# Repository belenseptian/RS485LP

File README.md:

-----

# RS-485LP (Low Power RS485 Node)

**RS-485LP** is an open-source RS485 converter featuring a custom PCB and optimized PlatformIO firmware. It is designed to minimize power consumption for battery-operated sensors and remote monitoring systems.

🔗 **Official Project Website:** [https://belenseptian.github.io/RS485LP/](https://belenseptian.github.io/RS485LP/)

-----

### 📟 Board Design Preview
Below are the top and bottom views of the RS-485LP PCB.

| Top View (Components) | Bottom View (Traces) |
| :---: | :---: |
|  |  |

-----

## 🚀 Features

  * **Sleep & Shutdown Optimization:** Optimized for deep-sleep and hardware shutdown modes to achieve micro-amp current draw during periods of inactivity.
  * **RS485 Protocol:** Reliable differential signaling for long-range data transmission.
  * **PlatformIO Integrated:** Easy-to-compile and upload firmware using VS Code.
  * **Compact Form Factor:** Small PCB footprint suitable for tight enclosures.

-----

## 🛠 Hardware Fabrication

### 1\. Obtain KiCad Files

The PCB design is created using **KiCad**. You can find the project files in the `pcb/` directory.

1.  Clone this repository to get the full KiCad project.
2.  Open the project in KiCad to view the schematic or modify the layout.

### 2\. Ordering from PCBWay (or similar)

Most modern PCB manufacturers allow you to upload the KiCad file directly:

1.  **Option A (Direct):** Upload the `.kicad_pcb` file from the `pcb/` folder directly to [PCBWay's Instant Quote](https://www.pcbway.com/).
2.  **Option B (Manual Gerber Export):** - In KiCad, go to **File \> Fabrication Outputs \> Gerbers (.gbr)**.
      - Generate the drill files and zip all outputs together.
      - Upload the resulting `.zip` file to the manufacturer.

-----

## 💻 Software Setup

This project uses **PlatformIO** inside **Visual Studio Code**.

### Prerequisites

  * **VS Code:** [Download here](https://code.visualstudio.com/)
  * **PlatformIO IDE Extension:** Install this via the VS Code Extensions marketplace.

### Project Installation

1.  Clone the repository:
    ```bash
    git clone https://github.com/belenseptian/RS485LP.git
    ```
2.  Open VS Code and go to **PlatformIO Home** \> **Open Project**.
3.  Navigate to the `firmware/` folder and select it.

-----

## 📤 Uploading & Testing Sleep Mode

1.  **Connect Hardware:** Connect your board to your computer using a USB-to-Serial adapter.
2.  **Build & Upload:** Use the **Checkmark (✅)** to compile and the **Arrow (➡️)** to flash.
3.  **Verify Shutdown:**
      - Open the **Serial Monitor (🔌)** (Baud rate: `115200`).
      - The monitor should display "Entering Sleep Mode..." or "Shutting Down...".
      - Use a Multimeter or Power Profiler to measure the current draw; it should drop significantly as the MCU enters the deep sleep/shutdown state.
4.  **Wake-up Trigger:** Ensure you have configured the wake-up source (e.g., Timer or External Interrupt on the RS485 RX pin).

-----

## 🔌 Wiring Diagram

| Pin Name | Description | Connection |
| :--- | :--- | :--- |
| **VCC** | Power Input | Depend on the sensor specifications |
| **GND** | Ground | Ground |
| **A** | RS485 Data+ | Connect to Bus A |
| **B** | RS485 Data- | Connect to Bus B |

-----

## 📂 Project Structure

```text
RS-485LP/
├── firmware/           # PlatformIO project files
│   ├── src/            # Main application code (Sleep/Shutdown logic)
│   └── platformio.ini  # Project configuration
├── pcb/                # KiCad project files (.kicad_pcb, .kicad_sch)
├── docs/               # Datasheets and additional documentation
└── README.md           # This file
```

-----

## 📜 License

This project is licensed under the **GNU General Public License v3.0** - see the [LICENSE](https://www.google.com/search?q=LICENSE) file for details.

## 🤝 Contributing

Contributions are welcome\! If you have suggestions for better power-gating or further reducing shutdown current, feel free to open an **Issue** or submit a **Pull Request**.

-----

**Developed by [Belen Septian](https://www.google.com/search?q=https://github.com/belenseptian)**

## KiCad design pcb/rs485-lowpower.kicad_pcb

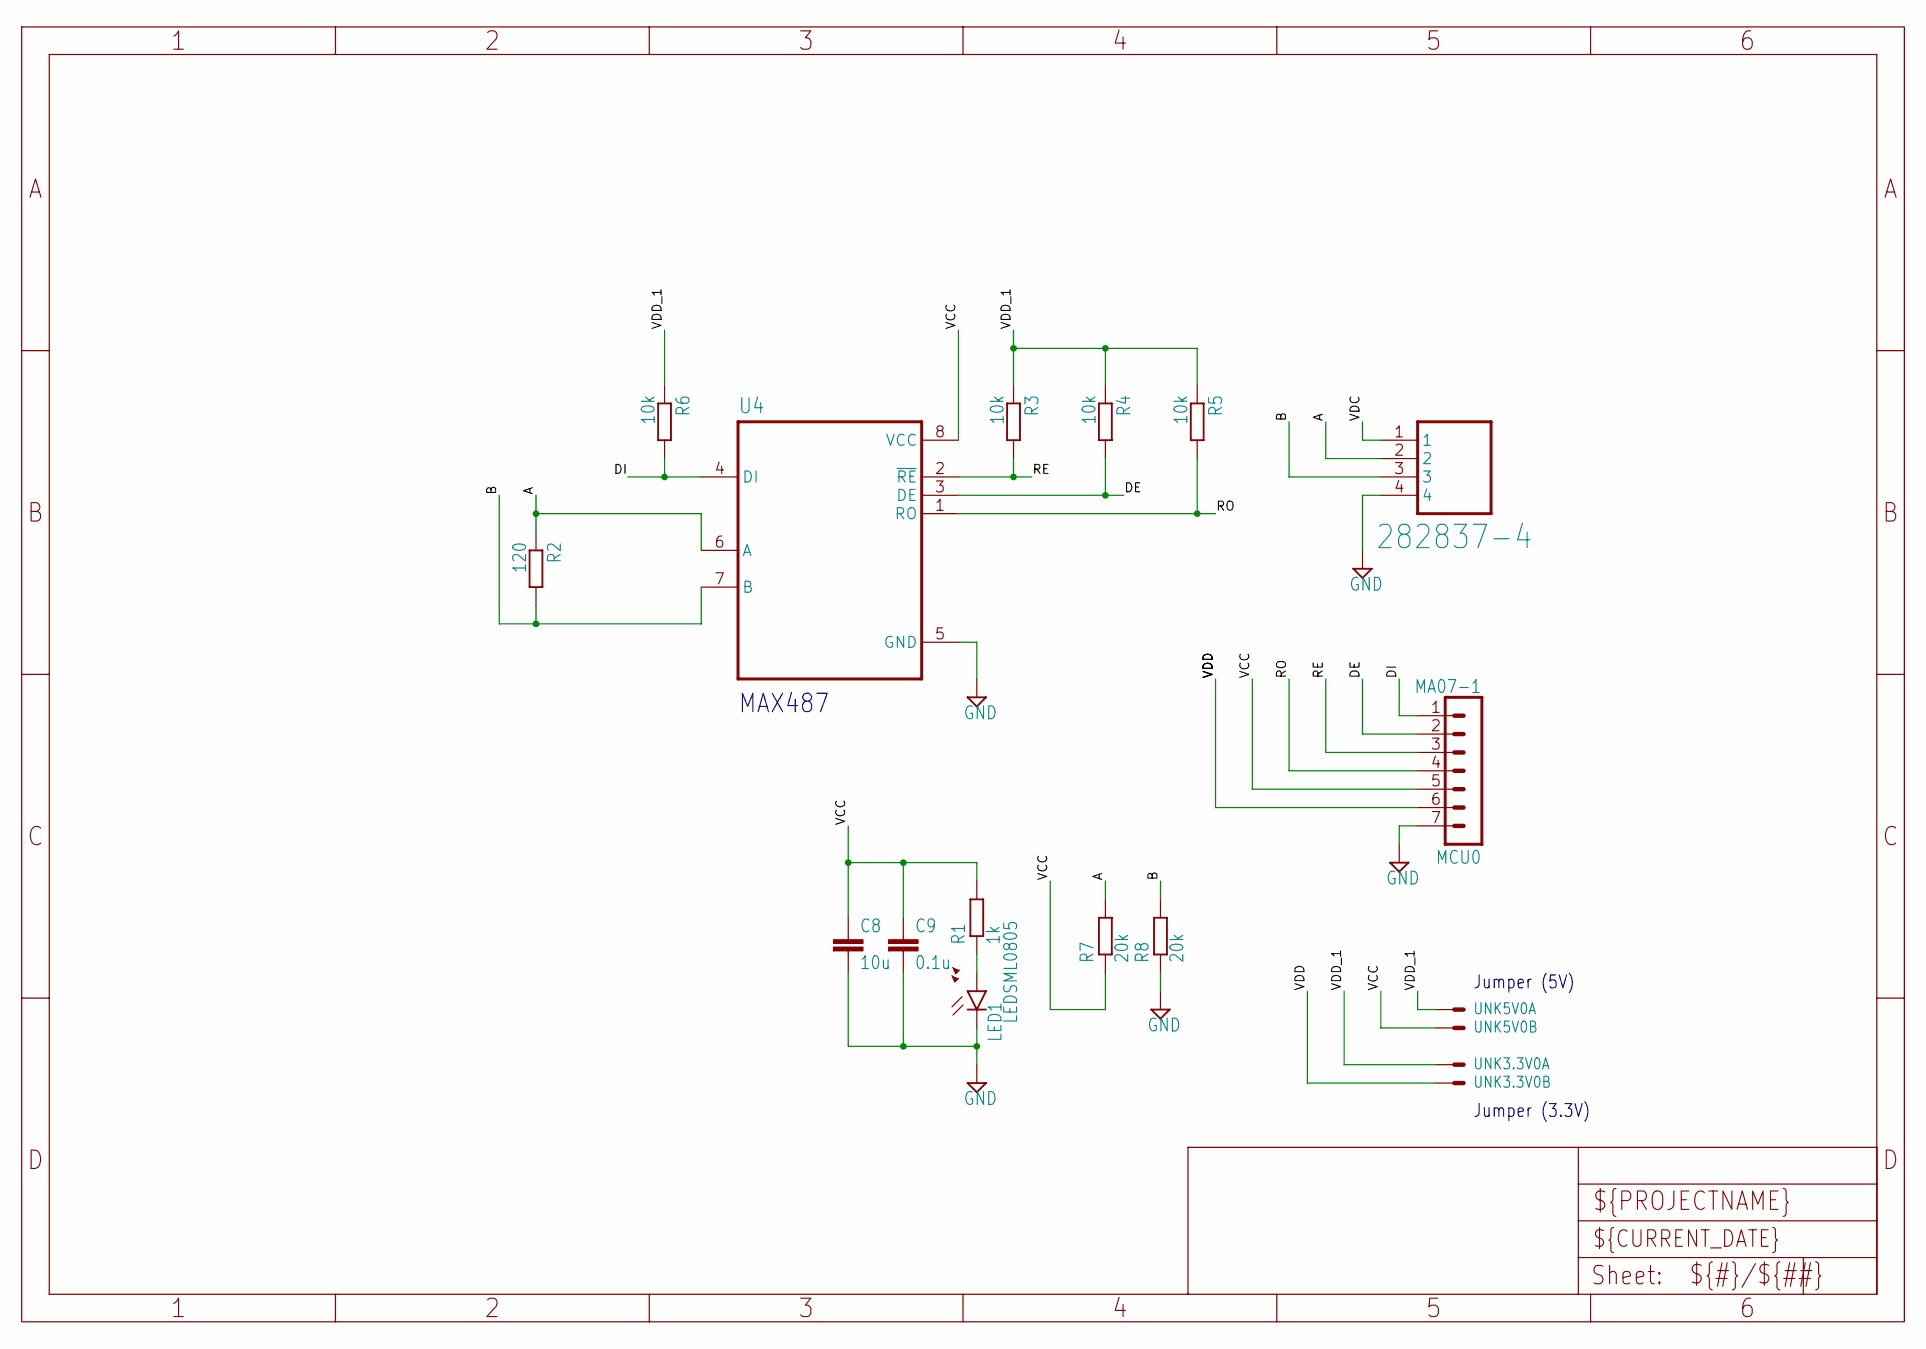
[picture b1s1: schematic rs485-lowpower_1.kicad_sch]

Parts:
C8: 10u; C1206
C9: 0.1u; C1206
LED1: LEDSML0805; SML0805
MCU0: MA07-1
R1: 1k; R0805
R2: 120; R0805
R3, R4, R5, R6: 10k; R0805
R7, R8: 20k; R0805
RS485-UGMLPV1.0: 282837-4; TE_282837-4
U4: MAX485CSA+T; SOIC127P600X175-8N
UNK3.3V0, UNK5V0: VAC; 22-23-2021

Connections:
A: R2.1, R7.2, RS485-UGMLPV1.0.2, U4.6 (A)
B: R2.2, R8.2, RS485-UGMLPV1.0.3, U4.7 (B)
DE: MCU0.2, R4.2, U4.3 (DE)
DI: MCU0.1, R6.2, U4.4 (DI)
GND: C8.2, C9.2, LED1.C, MCU0.7, R8.1, RS485-UGMLPV1.0.4, U4.5 (GND)
unnamed: LED1.A, R1.1
RE: MCU0.3, R3.2, U4.2 (~RE)
RO: MCU0.4, R5.2, U4.1 (RO)
VCC: C8.1, C9.1, MCU0.5, R1.2, R7.1, U4.8 (VCC), UNK5V0.2
VDC: RS485-UGMLPV1.0.1
VDD: MCU0.6, UNK3.3V0.2
VDD_1: R3.1, R4.1, R5.1, R6.1, UNK3.3V0.1, UNK5V0.1

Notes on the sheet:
Jumper (3.3V)
MAX487
Jumper (5V)

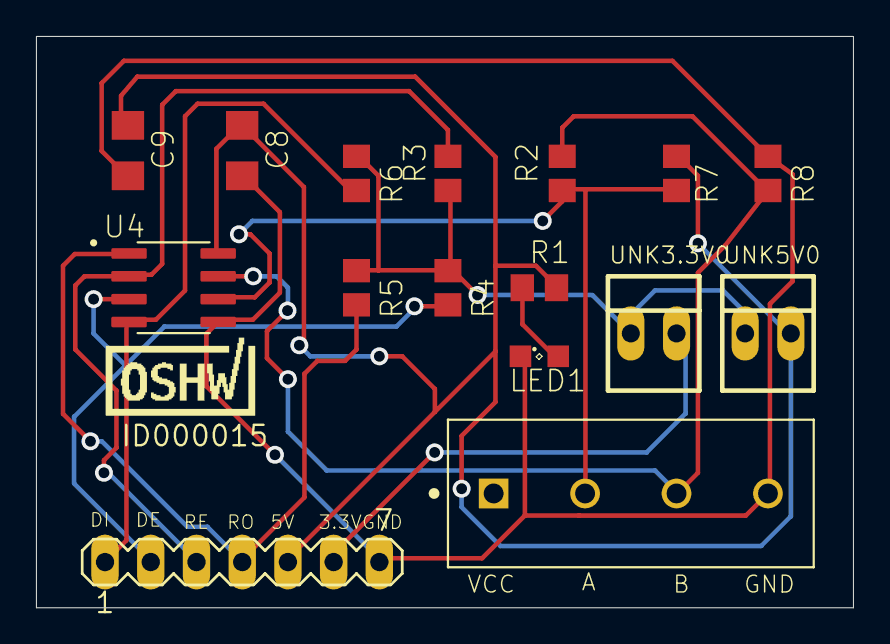
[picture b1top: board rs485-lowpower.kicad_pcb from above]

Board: 2 copper layers, 45.4 x 31.7 mm, 17 parts (0 on the bottom side), 11 nets.

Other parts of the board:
U$1: ID000015; CERT-SMALL-SILK

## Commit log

2026-04-10 add pcb and schematic designs
2026-04-10 Create LICENSE
2026-04-10 Update README to clarify PCB description
2026-04-10 edit readme
2026-04-10 reupload pcb file
2026-04-11 add gerber files
2026-04-12 modify main.cpp file
2026-04-16 rename to firmware
2026-04-16 add firmware folder

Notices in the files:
README.md:
[](https://www.gnu.org/licenses/gpl-3.0)
